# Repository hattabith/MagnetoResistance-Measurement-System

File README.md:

# MagnetoResistance-Measurement-System
A hardware–software system for measuring magnetoresistance of thin-film structures. The system performs automated experiment control, high-precision resistance measurements in a magnetic field, and provides data acquisition, analysis, and visualization.

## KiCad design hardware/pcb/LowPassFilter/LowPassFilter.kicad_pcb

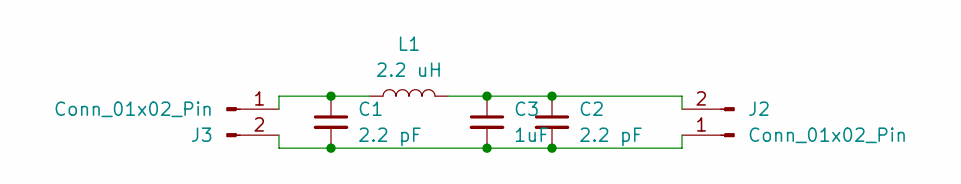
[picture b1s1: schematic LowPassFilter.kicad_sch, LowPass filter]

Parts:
C1, C2: 2.2 pF; C_Disc_D3.8mm_W2.6mm_P2.50mm
C3: 1uF; C_1206_3216Metric
J2, J3: Conn_01x02_Pin; JWT_A3963_1x02_P3.96mm_Vertical
L1: 2.2 uH; L_Bourns_SRR1208_12.7x12.7mm

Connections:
unnamed: C1.2, C2.2, C3.2, J2.1, J3.2
unnamed: C2.1, C3.1, J2.2, L1.2
unnamed: C1.1, J3.1, L1.1

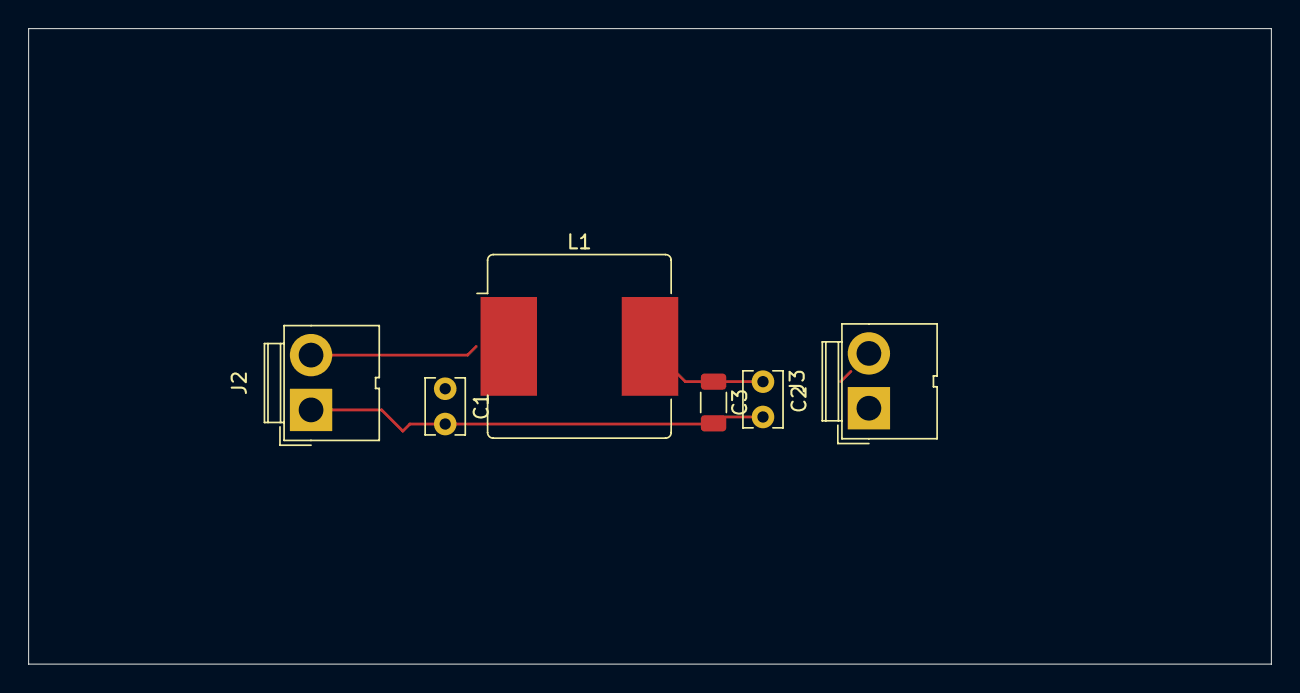
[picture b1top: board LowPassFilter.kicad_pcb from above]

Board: 2 copper layers, 88.0 x 45.0 mm, 6 parts (0 on the bottom side), 3 nets.

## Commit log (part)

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2026-03-13 Update copyright owner in LICENSE file
2026-03-13 init structure proj
2026-03-13 Update init proj
2026-03-13 Add WPF proj
2026-03-15 Add firmware proj
2026-03-15 Add base firmware
2026-03-16 Add proj WPF base options
2026-03-16 ADD color status and clear log
2026-03-16 add gitignore
2026-03-16 Add embeded tests
2026-03-20 tests repearing
